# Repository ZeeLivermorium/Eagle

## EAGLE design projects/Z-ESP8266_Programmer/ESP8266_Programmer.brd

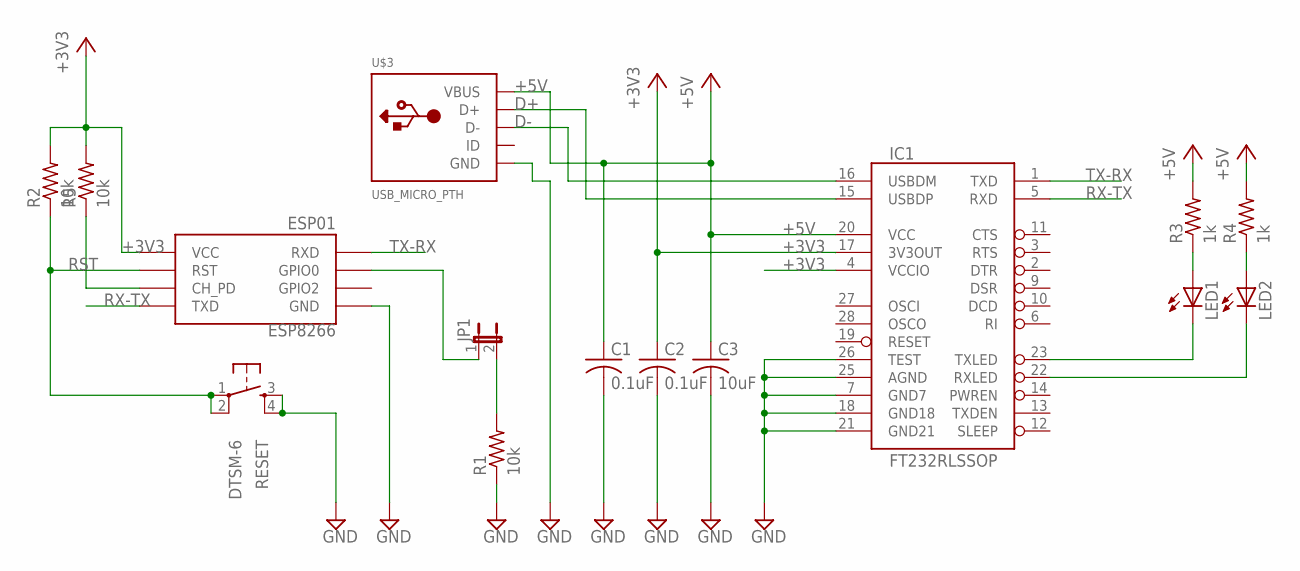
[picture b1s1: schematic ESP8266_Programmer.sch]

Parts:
C1, C2: 0.1uF; C0603
C3: 10uF; C1206
ESP8266: ESP01
IC1: FT232RLSSOP; SSOP28DB
JP1: JUMPER-2PTH; 1X02
LED1, LED2: LEDCHIP-LED0603; CHIP-LED0603
R1, R2, R5: 10k; R0603
R3, R4: 1k; R0603
RESET: DTSM-6
U$3: USB_MICRO_PTH

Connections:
+3V3: C2.1, ESP8266.VCC, IC1.4 (VCCIO), IC1.17 (3V3OUT), R2.2, R5.2
+5V: C1.1, C3.1, IC1.20 (VCC), R3.2, R4.2, U$3.1 (VBUS)
D+: IC1.15 (USBDP), U$3.3 (D+)
D-: IC1.16 (USBDM), U$3.2 (D-)
GND: C1.2, C2.2, C3.2, ESP8266.GND, IC1.7 (GND7), IC1.18 (GND18), IC1.21 (GND21), IC1.25 (AGND), IC1.26 (TEST), R1.1, RESET.3, RESET.4, U$3.5 (GND)
unnamed: ESP8266.CH_PD, R5.1
unnamed: JP1.2, R1.2
unnamed: ESP8266.GPIO0, JP1.1
unnamed: LED1.A, R3.1
unnamed: LED2.A, R4.1
unnamed: IC1.23 (TXLED), LED1.C
unnamed: IC1.22 (RXLED), LED2.C
RST: ESP8266.RST, R2.1, RESET.1, RESET.2
RX-TX: ESP8266.TX (TXD), IC1.5 (RXD)
TX-RX: ESP8266.RX (RXD), IC1.1 (TXD)

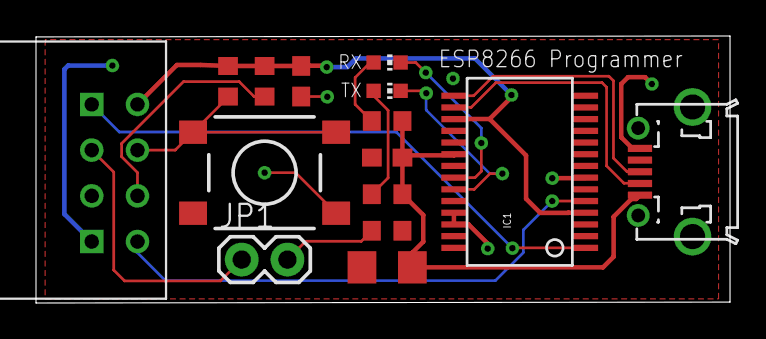
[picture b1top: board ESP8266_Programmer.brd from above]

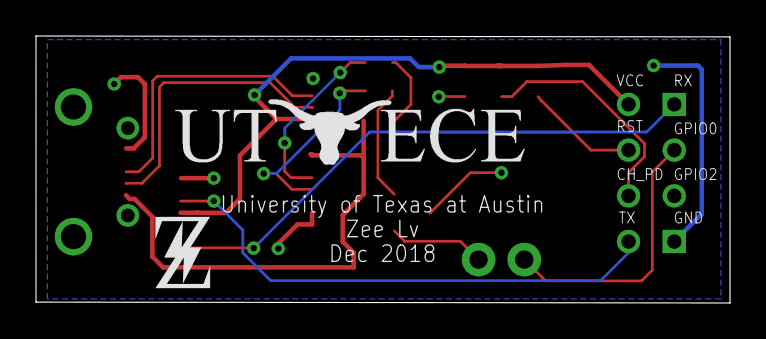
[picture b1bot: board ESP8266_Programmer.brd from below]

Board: 2 copper layers, 38.6 x 14.8 mm, 17 parts (2 on the bottom side), 15 nets.

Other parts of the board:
U$1: Z_LOGO
U$2: UT_ECE_LOGO

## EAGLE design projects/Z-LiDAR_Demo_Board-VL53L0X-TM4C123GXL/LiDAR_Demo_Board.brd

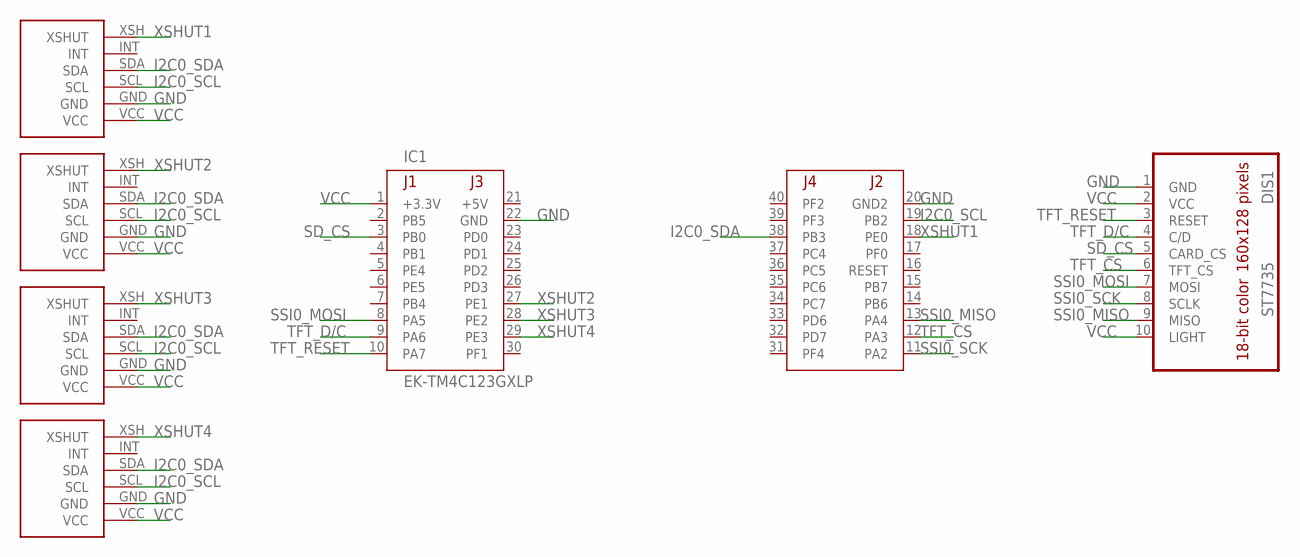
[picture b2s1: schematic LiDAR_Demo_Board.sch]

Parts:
DIS1: ST7735
IC1: EK-TM4C123GXLP; TM4C123LAUNCHPAD
U$1, U$2, U$3, U$4: VL53L0X_ATK

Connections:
+5V: IC1.21 (+5V)
GND: DIS1.1 (GND), IC1.20 (GND2), IC1.22 (GND), U$1.GND, U$2.GND, U$3.GND, U$4.GND
I2C0_SCL: IC1.19 (PB2), U$1.SCL, U$2.SCL, U$3.SCL, U$4.SCL
I2C0_SDA: IC1.38 (PB3), U$1.SDA, U$2.SDA, U$3.SDA, U$4.SDA
SD_CS: DIS1.5 (CARD_CS), IC1.3 (PB0)
SSI0_MISO: DIS1.9 (MISO), IC1.13 (PA4)
SSI0_MOSI: DIS1.7 (MOSI), IC1.8 (PA5)
SSI0_SCK: DIS1.8 (SCLK), IC1.11 (PA2)
TFT_CS: DIS1.6 (TFT_CS), IC1.12 (PA3)
TFT_D/C: DIS1.4 (C/D), IC1.9 (PA6)
TFT_RESET: DIS1.3 (RESET), IC1.10 (PA7)
VCC: DIS1.2 (VCC), DIS1.10 (LIGHT), IC1.1 (+3.3V), U$1.VCC, U$2.VCC, U$3.VCC, U$4.VCC
XSHUT1: IC1.18 (PE0), U$1.XSH (XSHUT)
XSHUT2: IC1.27 (PE1), U$2.XSH (XSHUT)
XSHUT3: IC1.28 (PE2), U$3.XSH (XSHUT)
XSHUT4: IC1.29 (PE3), U$4.XSH (XSHUT)

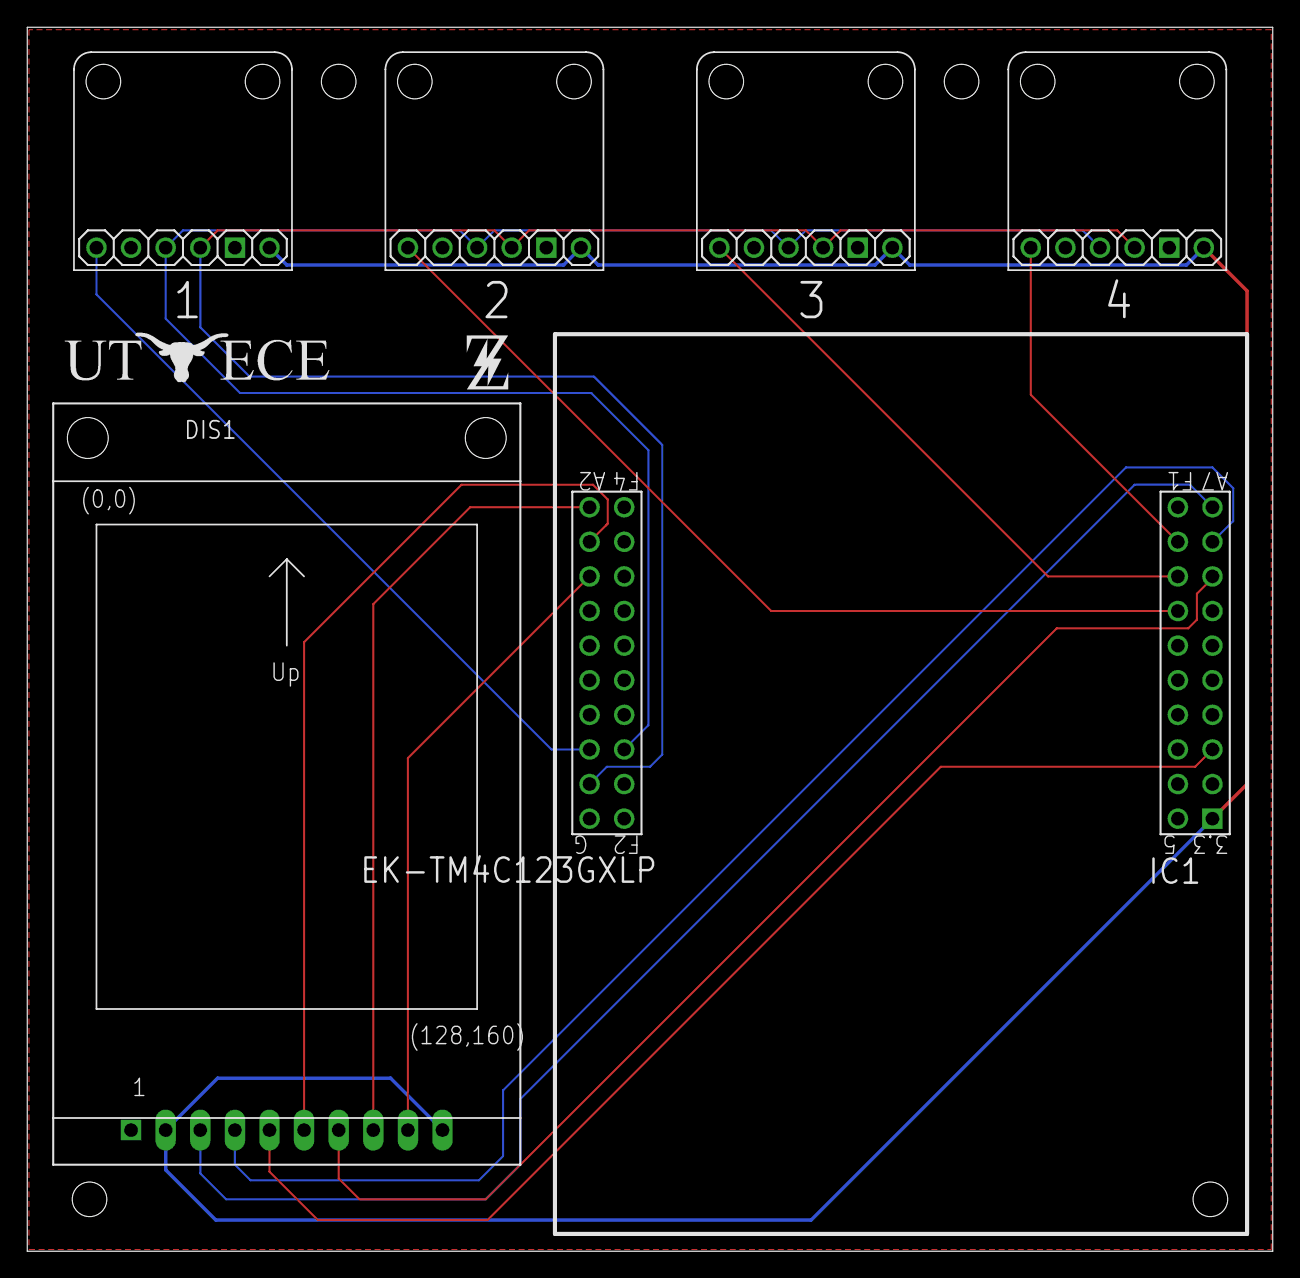
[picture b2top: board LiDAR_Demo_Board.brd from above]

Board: 2 copper layers, 91.4 x 89.8 mm, 9 parts (1 on the bottom side), 15 nets.

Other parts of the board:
U$5, U$7: LOGO_UT_ECE_20X4
U$6: LOGO_Z_3X4

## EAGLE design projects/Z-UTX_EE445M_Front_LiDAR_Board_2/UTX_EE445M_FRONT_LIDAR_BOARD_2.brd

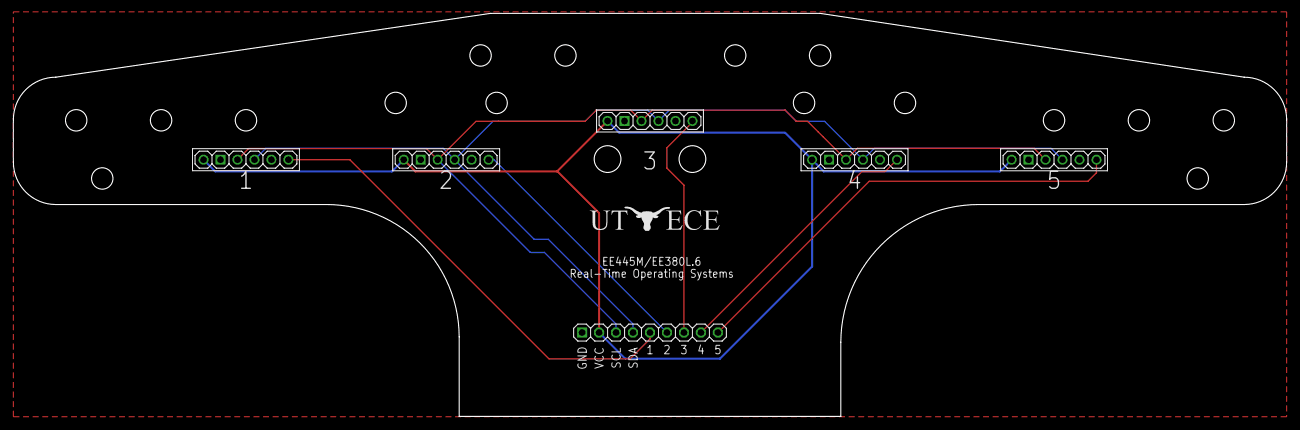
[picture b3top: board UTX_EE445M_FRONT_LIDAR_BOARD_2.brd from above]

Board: 2 copper layers, 190.5 x 60.3 mm, 8 parts (1 on the bottom side), 9 nets.

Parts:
U$1: UTX_EE445M_LIDAR_FRONT_BOARD_CONNECTOR_PTH
U$2, U$3, U$4, U$5, U$6: LIDAR_VL53L0X_ATK_VERT
U$7: LOGO_UT_ECE_20X4
U$8: LOGO_Z_3X4

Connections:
GND: U$1.GND, U$2.GND, U$3.GND, U$4.GND, U$5.GND, U$6.GND
SCL: U$1.SCL, U$2.SCL, U$3.SCL, U$4.SCL, U$5.SCL, U$6.SCL
SDA: U$1.SDA, U$2.SDA, U$3.SDA, U$4.SDA, U$5.SDA, U$6.SDA
VCC: U$1.VCC, U$2.VCC, U$3.VCC, U$4.VCC, U$5.VCC, U$6.VCC
XSHUT1: U$1.XSHUT1, U$2.XSH
XSHUT2: U$1.XSHUT2, U$3.XSH
XSHUT3: U$1.XSHUT3, U$4.XSH
XSHUT4: U$1.XSHUT4, U$5.XSH
XSHUT5: U$1.XSHUT5, U$6.XSH

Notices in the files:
parts and their libraries:
SparkFun: Licensing: CC v3.0 Share-Alike You are welcome to use this library for commercial purposes.
